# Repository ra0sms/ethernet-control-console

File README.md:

# Ethernet control console

A device for controlling 8 outputs over Ethernet using a built-in web interface. The main outputs switch voltage, and each one is duplicated by an open-collector output.

It is built on an STM32F401 (Black Pill) and a W5500 Ethernet controller. You can configure it over USB with a console or the GUI application.

- Wi-Fi version with the same functionality: [ESP8266_antenna_switch](https://github.com/ra0sms/ESP8266_antenna_switch)
- More information: https://ra0sms.com/ethernet-control-console

## Specifications

| Parameter | Value |
|---|---|
| Input voltage | 5–45 V DC |
| Output current | 500 mA total for all 8 outputs (and 500 mA total for open-collector outputs) |
| Interface | Ethernet 10/100 (W5500), USB (virtual COM port) |
| MCU | STM32F401CCU6 / STM32F401CEU6 (Black Pill) |
| PCB size | 78 × 88 mm |

## Operating modes

You select the mode in the web interface. It is saved together with the other settings.

| Mode | Behavior |
|---|---|
| **Toggle** | Each output toggles independently |
| **Switch** | Only one output is on at a time; turning one on turns the others off |
| **Dual** | Outputs 1–4 and 5–8 form two groups, each with its own Toggle/Switch mode |

## Firmware

Prebuilt firmware is in [firmware/](firmware/):

- `w5500_outlet.hex` – contains its own addresses
- `w5500_outlet.bin` – write to address `0x08000000`

### Flashing with ST-Link

STM32CubeProgrammer:

```sh
STM32_Programmer_CLI -c port=SWD -w firmware/w5500_outlet.hex -v -rst
```

st-flash:

```sh
st-flash --reset write firmware/w5500_outlet.bin 0x08000000
```

### Flashing over USB (DFU)

1. Hold **BOOT0**, press and release **NRST**, then release BOOT0.
2. Flash with STM32CubeProgrammer (`-c port=USB1`) or `dfu-util`:

```sh
dfu-util -a 0 -s 0x08000000:leave -D firmware/w5500_outlet.bin
```

> Settings are stored in flash sector 5 (`0x08020000`–`0x0803FFFF`), separately from the firmware. A normal firmware update keeps the settings. A full chip erase resets them to defaults.

## Default settings

| Parameter | Value |
|---|---|
| IP | 192.168.0.250 |
| Subnet mask | 255.255.255.0 |
| Gateway | 192.168.0.1 |
| DNS | 8.8.8.8 |
| MAC | 00:08:DC:AB:CD:EF |
| Web login / password | `admin` / `password` |

If you use more than one device on the same network, give each one its own IP and MAC address.

## Web interface

Open `http://<device IP>/` in a browser and log in (HTTP Basic Auth).

## USB configuration

When you connect the board over USB, it appears as a virtual COM port (STM32 Virtual ComPort). Any port speed works.

You can configure it without the W5500 or the rest of the circuit: a bare Black Pill on USB is enough. The firmware detects the W5500 automatically and starts the web server when the module is connected.

### Configuration software

[gui/](gui/) contains a GUI application: `gui.py` (Python 3, `pyserial`, `PyQt5`) and a Windows build in `gui-lan.zip`.

### Console commands

| Command | Description |
|---|---|
| `help` | List commands |
| `network` | Show network settings |
| `set ip <x.x.x.x>` | Set IP address |
| `set subnet <x.x.x.x>` | Set subnet mask (alias: `sn`) |
| `set gateway <x.x.x.x>` | Set gateway (alias: `gw`) |
| `set dns <x.x.x.x>` | Set DNS server |
| `set mac <xx:xx:xx:xx:xx:xx>` | Set MAC address |
| `set user <name>` | Set web login (1–31 characters) |
| `set pass <password>` | Set web password (up to 31 characters) |
| `get <ip\|mac\|subnet\|gateway\|dns\|user\|pass>` | Show a parameter |
| `buttons` | Show output names |
| `setbutton <0-7> <name>` | Rename an output (up to 15 characters) |
| `save` | Save settings to flash |
| `load` | Load settings from flash |
| `default` | Reset to factory defaults and save |
| `reset` | Reboot the device |

Changes take effect immediately, but they are saved only after `save`.

Example:

```
set ip 192.168.1.50
set gateway 192.168.1.1
setbutton 0 Antenna1
save
reset
```

## Hardware

### Schematic

### Pinout

| Function | STM32 pins |
|---|---|
| Outputs 1–8 | PB0–PB7 |
| W5500 SPI (SCK / MISO / MOSI) | PA5 / PA6 / PA7 |
| W5500 CS | PA4 |
| W5500 RST | PA3 |
| Status LED | PC13 |

### Boxed version

## Building from source

The project is in [code/](code/) and is built with STM32CubeIDE (open `code/` as an existing project). PCB files are in [KiCad/](KiCad/).

To build from the command line, use the toolchain bundled with STM32CubeIDE (the generic `arm-none-eabi-gcc` does not support the `-fcyclomatic-complexity` flag):

```sh
export PATH=/opt/st/stm32cubeide_<version>/plugins/com.st.stm32cube.ide.mcu.externaltools.gnu-tools-for-stm32.<version>/tools/bin:$PATH
cd code/Debug && make -j8 all
```

## License

See [LICENSE](LICENSE).

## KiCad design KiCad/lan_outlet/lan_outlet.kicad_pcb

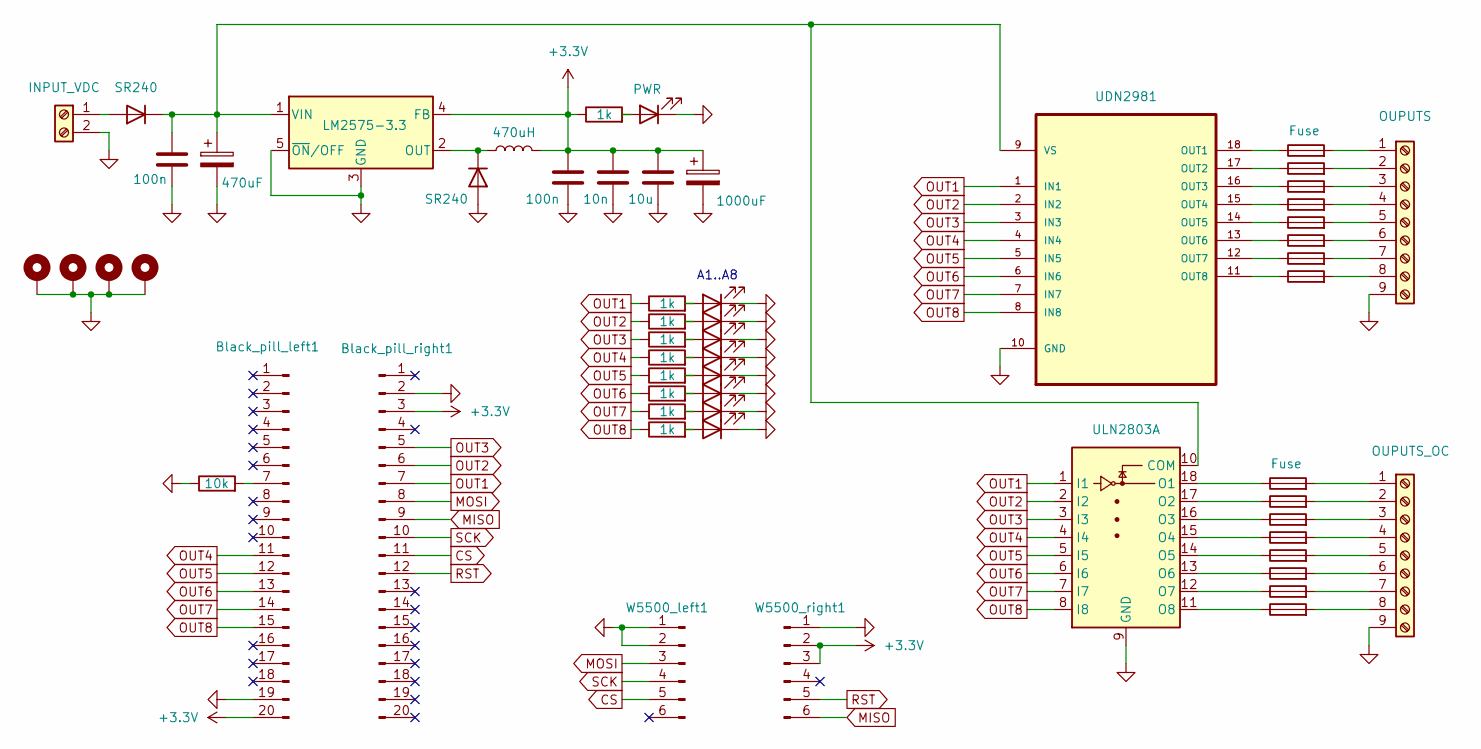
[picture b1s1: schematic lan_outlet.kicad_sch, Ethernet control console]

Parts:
Black_pill_left1: Conn_01x20_Pin; PinHeader_1x20_P2.54mm_Vertical
Black_pill_right1: Conn_01x20_Pin; PinHeader_1x20_P2.54mm_Vertical
C1, C3: 100n; C_1206_3216Metric
C2: 470uF; CP_Radial_D10.0mm_P5.00mm
C4: 10n; C_1206_3216Metric
C5: 10u; C_1206_3216Metric
C6: 1000uF; CP_Radial_D8.0mm_P3.80mm
D1, D2: SR240; D_DO-41_SOD81_P10.16mm_Horizontal
D3: PWR; D_1206_3216Metric
D4, D5, D6, D7, D8, D9, D10, D11: A1; D_1206_3216Metric
F1, F2, F3, F4, F5, F6, F7, F8, F9, F10, F11, F12, F13, F14, F15, F16: Fuse; R_1206_3216Metric
H1, H2, H3, H4: MountingHole_Pad; MountingHole_3.2mm_M3_Pad
J1: INPUT_VDC; TerminalBlock_MetzConnect_Type055_RT01502HDWU_1x02_P5.00mm_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
J2: OUPUTS; TerminalBlock_MaiXu_MX126-5.0-09P_1x09_P5.00mm
J3: OUPUTS_OC; TerminalBlock_MaiXu_MX126-5.0-09P_1x09_P5.00mm
L1: 470uH; L_Radial_D10.0mm_P5.00mm_Neosid_SD12_style3
R1: 10k; R_1206_3216Metric
R2, R3, R4, R5, R6, R7, R8, R9, R10: 1k; R_1206_3216Metric
U1: LM2575-3.3; TO-220-5_Vertical
U2: UDN2981; DIP-18_W7.62mm_LongPads; MPN UDN2981
U3: ULN2803A; DIP-18_W7.62mm_LongPads
W5500_left1, W5500_right1: Conn_01x06_Pin; PinHeader_1x06_P2.54mm_Vertical

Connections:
+3.3V: Black_pill_left1.20, Black_pill_right1.3, C3.1, C4.1, C5.1, C6.1, L1.2, R2.1, U1.4 (FB), W5500_right1.2, W5500_right1.3
CS: Black_pill_right1.11, W5500_left1.5
GND: Black_pill_left1.19, Black_pill_right1.2, C1.2, C2.2, C3.2, C4.2, C5.2, C6.2, D2.2 (A), D3.1 (K), D4.1 (K), D5.1 (K), D6.1 (K), D7.1 (K), D8.1 (K), D9.1 (K), D10.1 (K), D11.1 (K), H1.1, H2.1, H3.1, H4.1, J1.2, J2.9, J3.9, R1.1, U1.3 (GND), U1.5 (~ON/OFF), U2.10 (GND), U3.9 (GND), W5500_left1.1, W5500_left1.2, W5500_right1.1
MISO: Black_pill_right1.9, W5500_right1.6
MOSI: Black_pill_right1.8, W5500_left1.3
unnamed: Black_pill_left1.7, R1.2
unnamed: D1.2 (A), J1.1
unnamed: C1.1, C2.1, D1.1 (K), U1.1 (VIN), U2.9 (VS), U3.10 (COM)
unnamed: D2.1 (K), L1.1, U1.2 (OUT)
unnamed: D3.2 (A), R2.2
unnamed: D4.2 (A), R3.2
unnamed: D5.2 (A), R4.2
unnamed: D6.2 (A), R5.2
unnamed: D7.2 (A), R6.2
unnamed: D8.2 (A), R7.2
unnamed: D9.2 (A), R8.2
unnamed: D10.2 (A), R9.2
unnamed: D11.2 (A), R10.2
unnamed: F9.2, J2.1
unnamed: F10.2, J2.2
unnamed: F11.2, J2.3
unnamed: F12.2, J2.4
unnamed: F13.2, J2.5
unnamed: F14.2, J2.6
unnamed: F15.2, J2.7
unnamed: F16.2, J2.8
unnamed: F1.2, J3.1
unnamed: F2.2, J3.2
unnamed: F3.2, J3.3
unnamed: F4.2, J3.4
unnamed: F5.2, J3.5
unnamed: F6.2, J3.6
unnamed: F7.2, J3.7
unnamed: F8.2, J3.8
unnamed: F9.1, U2.18 (OUT1)
unnamed: F10.1, U2.17 (OUT2)
unnamed: F11.1, U2.16 (OUT3)
unnamed: F12.1, U2.15 (OUT4)
unnamed: F13.1, U2.14 (OUT5)
unnamed: F14.1, U2.13 (OUT6)
unnamed: F15.1, U2.12 (OUT7)
unnamed: F16.1, U2.11 (OUT8)
unnamed: F1.1, U3.18 (O1)
unnamed: F2.1, U3.17 (O2)
unnamed: F3.1, U3.16 (O3)
unnamed: F4.1, U3.15 (O4)
unnamed: F5.1, U3.14 (O5)
unnamed: F6.1, U3.13 (O6)
unnamed: F7.1, U3.12 (O7)
unnamed: F8.1, U3.11 (O8)
OUT1: Black_pill_right1.7, R3.1, U2.1 (IN1), U3.1 (I1)
OUT2: Black_pill_right1.6, R4.1, U2.2 (IN2), U3.2 (I2)
OUT3: Black_pill_right1.5, R5.1, U2.3 (IN3), U3.3 (I3)
OUT4: Black_pill_left1.11, R6.1, U2.4 (IN4), U3.4 (I4)
OUT5: Black_pill_left1.12, R7.1, U2.5 (IN5), U3.5 (I5)
OUT6: Black_pill_left1.13, R8.1, U2.6 (IN6), U3.6 (I6)
OUT7: Black_pill_left1.14, R9.1, U2.7 (IN7), U3.7 (I7)
OUT8: Black_pill_left1.15, R10.1, U2.8 (IN8), U3.8 (I8)
RST: Black_pill_right1.12, W5500_right1.5
SCK: Black_pill_right1.10, W5500_left1.4

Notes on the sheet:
A1..A8

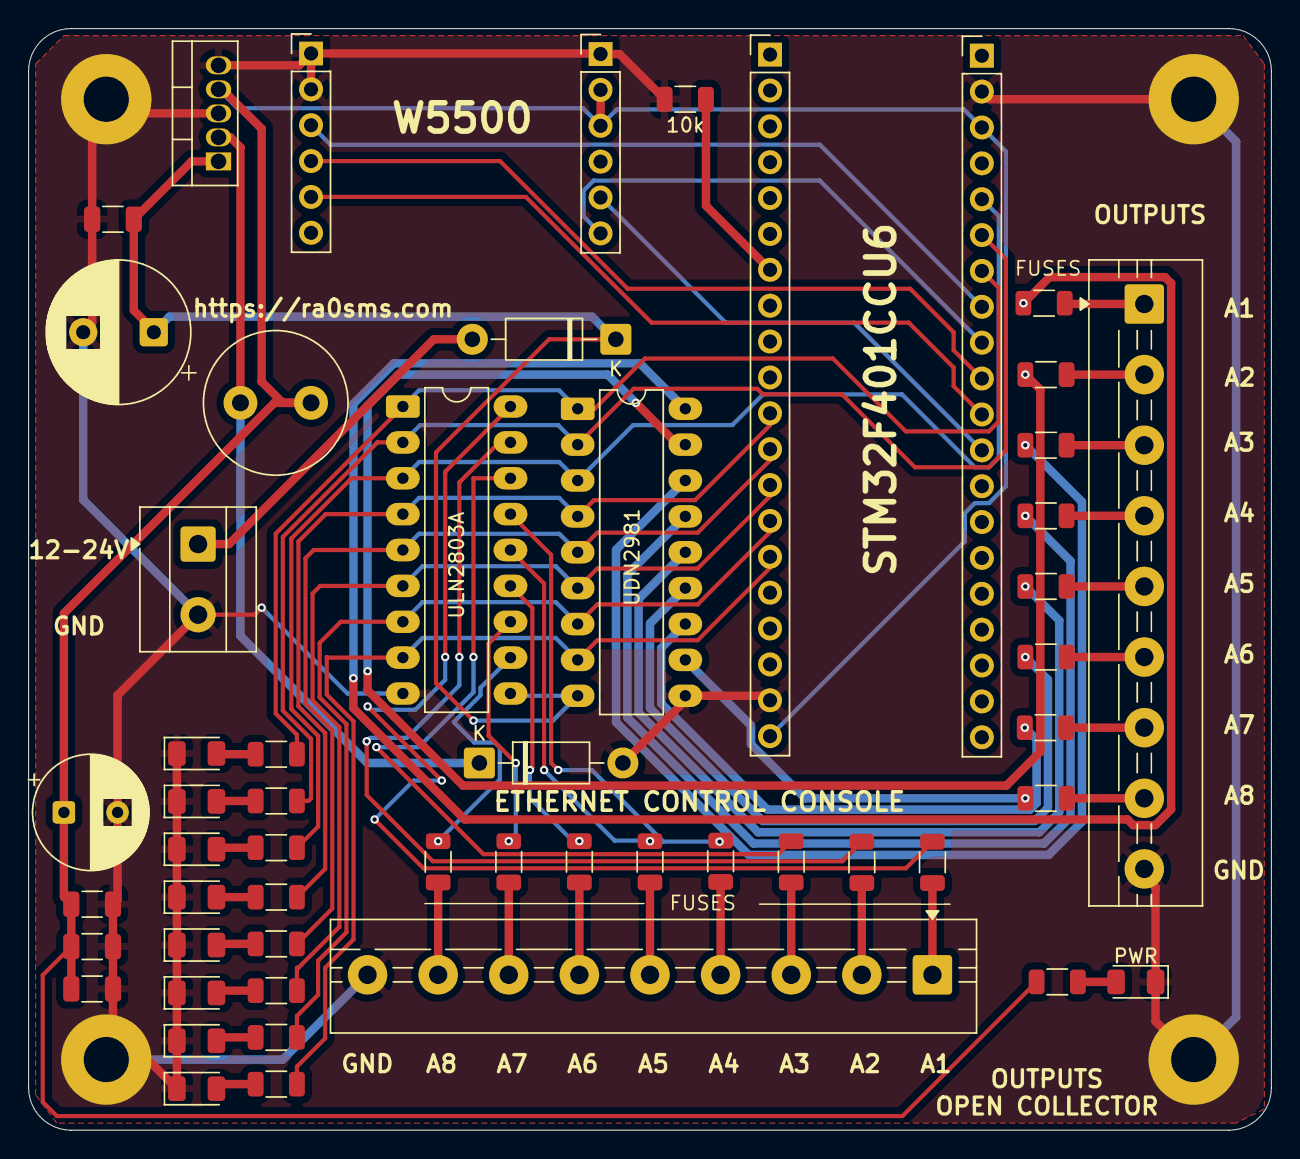
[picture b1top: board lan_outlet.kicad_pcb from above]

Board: 2 copper layers, 88.0 x 78.0 mm, 58 parts (0 on the bottom side), 60 nets.

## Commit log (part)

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2025-11-10 write readme
2025-11-12 fix some issues with http requests
2026-04-27 fix some issuies
2026-05-17 add Dual mode
